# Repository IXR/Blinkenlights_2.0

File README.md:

Blinkenlights_2.0
=================
Learn to Solder Kit - DER BLINKENLIGHTS

Der Blinkenlights "Learn To Solder" kit is a basic oscillator circuit (astable multivibrator) driving two LEDs for an alternating light flashing effect. The kit is designed to be a low-cost, entry level project to teach the basics of soldering. It is intended for those who have never soldered before, and is simple enough that even young children should be able to assemble it (with supervision). Furthermore, it has a nice variety of basic electronic components, so it is a good introduction to electronics as well.

Goals for this kit are:
* Simplicity - any beginner should be able to do it, and it should not take a very long time
* Sufficient learning experience - it should not be so simple that the student doesn't learn much. 1 LED on a battery does not provide much learning.
* Low cost - it should be cheap enough that it's a no-brainer for cost vs. benefit. Also, to make it cost-suitable for scout troops or school classes. $5-$10 range.
* Income source - There should be enough margin to make it a nice fund-raiser item for IXR

The kit contains:
* 1x printed circuit board
* 2x 100KΩ resistors (1/4W 5% carbon-film)
* 2x 220Ω resistors (1/4W 5% carbon-film)
* 2x NPN transistors (2N3904, TO-92-3 Kinked Lead)
* 2x 10μF, 16V capacitors (radial, general purpose, 4x7mm case)
* 2x light-emitting diodes (5mm, red or green)
* 1x battery holder (Keystone 3002, 20mm coin cell, surface mount)
* 1x CR2032 Battery (3V, 20x3.2mm, 200mA)

License:
CC-BY-SA - This work is licensed under a Creative Commons Attribution-ShareAlike 3.0 Unported License.

WIKI:
For more information, visit the wiki page at http://wiki.ixrnj.org/index.php?title=Blinkenlights

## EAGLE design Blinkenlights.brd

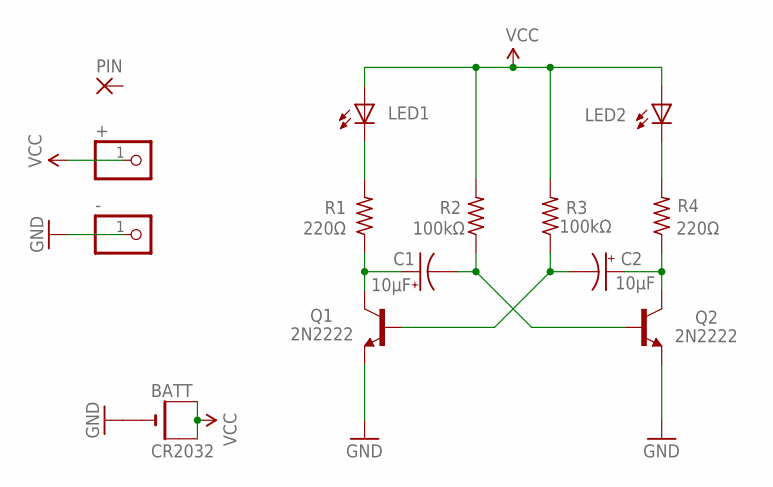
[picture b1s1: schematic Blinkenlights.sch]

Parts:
+: PINHD-1X1CB; 1X01-CLEANBIG
-: PINHD-1X1CB; 1X01-CLEANBIG
BATT: CR2032; CR2032-SMD
C1, C2: 10μF; E-2.54-05
LED1, LED2: LED5MM_BIG
PIN: 3,17/1,3
Q1, Q2: 2N2222; TO92-EBC-OVAL
R1, R4: 220Ω; 0207/10_BIG
R2, R3: 100kΩ; 0207/10_BIG

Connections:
GND: -.1, BATT.-, Q1.E, Q2.E
unnamed: C1.+, Q1.C, R1.1
unnamed: C2.+, Q2.C, R4.1
unnamed: C1.-, Q2.B, R2.1
unnamed: C2.-, Q1.B, R3.1
unnamed: LED1.K (C), R1.2
unnamed: LED2.K (C), R4.2
VCC: +.1, BATT.+$1 (+), BATT.+$2 (+1), LED1.A, LED2.A, R2.2, R3.2

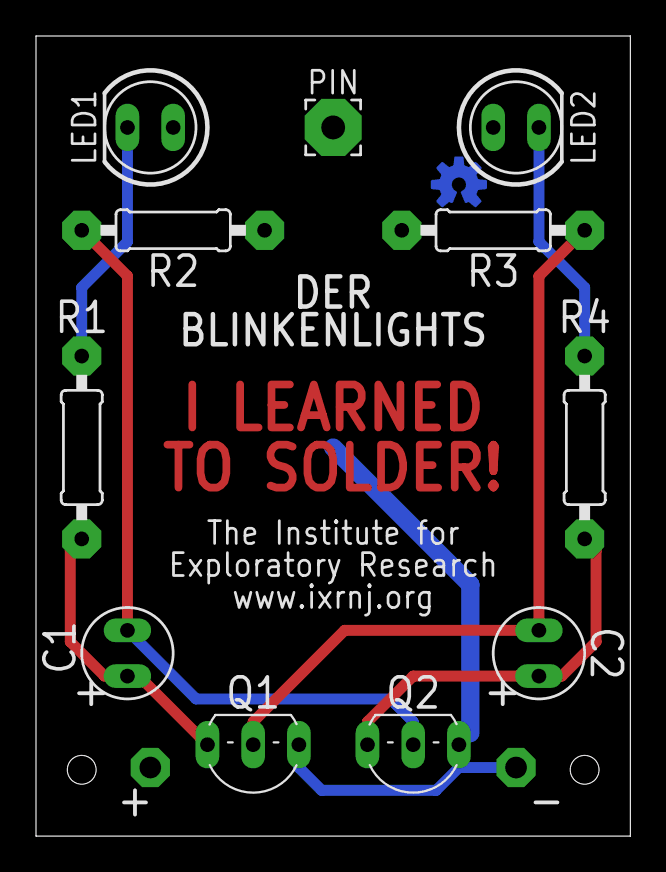
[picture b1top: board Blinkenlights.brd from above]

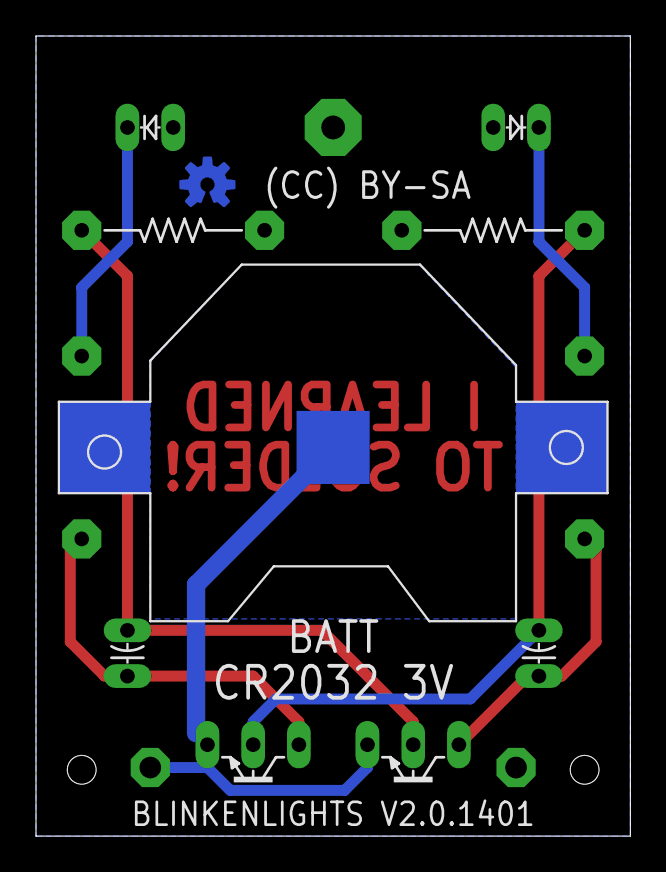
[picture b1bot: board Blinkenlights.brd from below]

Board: 2 copper layers, 33.0 x 44.5 mm, 15 parts (2 on the bottom side), 8 nets.

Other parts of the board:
U$1: OSHW-LOGO-S

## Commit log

2013-06-10 Initial Fileload
    Version 2.0613
2013-09-06 2.0.0913 Version updates
    Minor modifications and tweaking
2014-01-31 v2.0.1401 Flipped battery clip - could not insert battery when lapel pin was installed.

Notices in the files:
parts and their libraries:
SparkFun: Licensing: CC v3.0 Share-Alike You are welcome to use this library for commercial purposes.
